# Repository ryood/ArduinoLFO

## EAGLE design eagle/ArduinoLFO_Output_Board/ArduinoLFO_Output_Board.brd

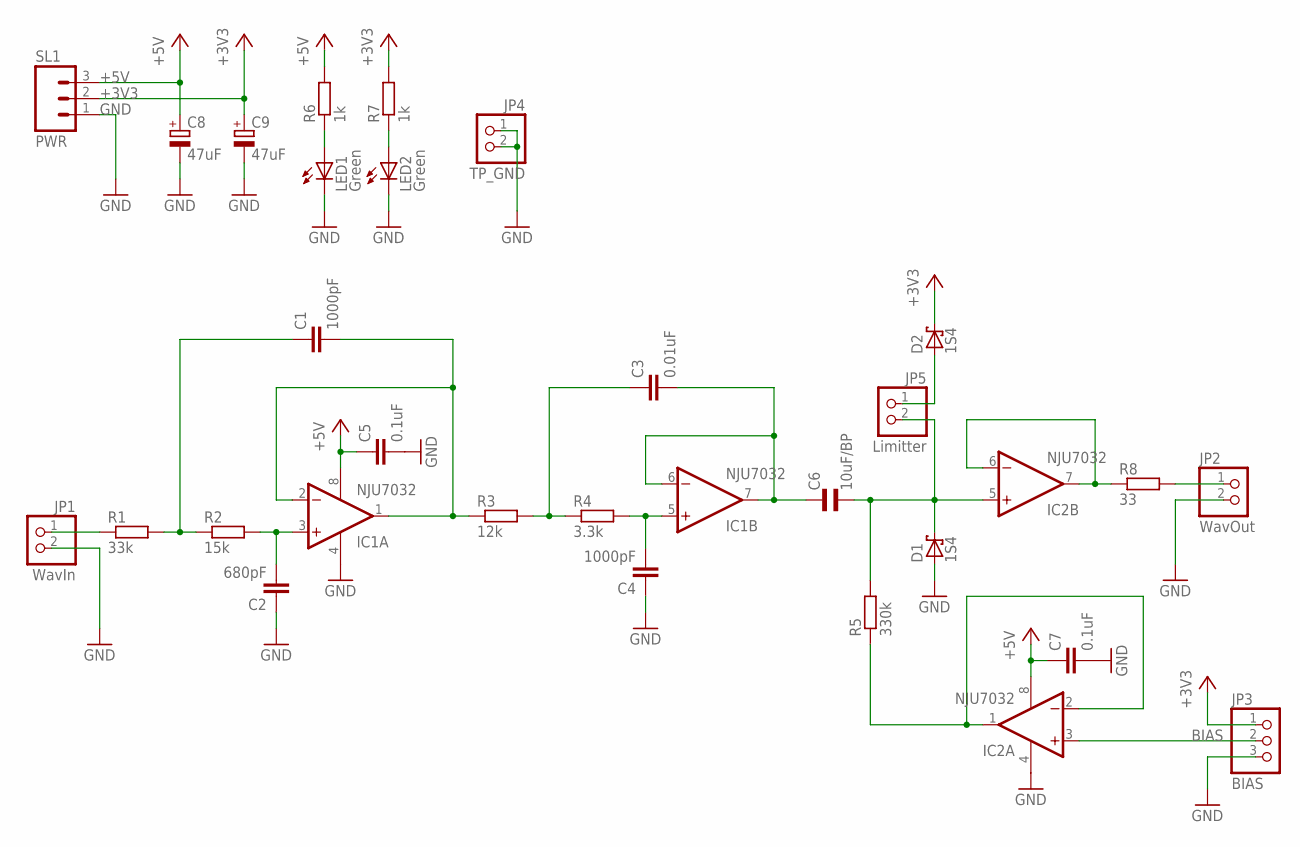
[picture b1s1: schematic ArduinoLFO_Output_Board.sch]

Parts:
C1, C4: 1000pF; C050-025X075
C2: 680pF; C050-030X075
C3: 0.01uF; C050-025X075
C5, C7: 0.1uF; C025-024X044
C6: 10uF/BP; E5-8,5
C8, C9: 47uF; E2,5-6
D1, D2: 1S4; DO35-7
IC1, IC2: NJU7032; DIL08
JP1: WavIn; 1X02
JP2: WavOut; 1X02
JP3: BIAS; 1X03
JP4: TP_GND; 1X02
JP5: Limitter; 1X02
LED1, LED2: Green; LED3MM
R1: 33k; 0207/7
R2: 15k; 0207/7
R3: 12k; 0207/7
R4: 3.3k; 0207/7
R5: 330k; 0207/7
R6, R7: 1k; 0207/7
R8: 33; 0207/7
SL1: PWR; 03PA

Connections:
+3V3: C9.+, D2.C, JP3.1, R7.2, SL1.2
+5V: C5.1, C7.1, C8.+, IC1.8 (V+), IC2.8 (V+), R6.2, SL1.3
BIAS: IC2.3 (+IN), JP3.2
GND: C2.1, C4.1, C5.2, C7.2, C8.-, C9.-, D1.A, IC1.4 (V-), IC2.4 (V-), JP1.2, JP2.2, JP3.3, JP4.1, JP4.2, LED1.K (C), LED2.K (C), SL1.1
unnamed: JP1.1, R1.1
unnamed: C1.1, R1.2, R2.1
unnamed: C2.2, IC1.3 (+IN), R2.2
unnamed: C1.2, IC1.1 (OUT), IC1.2 (-IN), R3.1
unnamed: C3.1, R3.2, R4.1
unnamed: C4.2, IC1.5 (+IN), R4.2
unnamed: C3.2, C6.1, IC1.6 (-IN), IC1.7 (OUT)
unnamed: C6.2, D1.C, IC2.5 (+IN), JP5.2, R5.2
unnamed: IC2.6 (-IN), IC2.7 (OUT), R8.1
unnamed: IC2.1 (OUT), IC2.2 (-IN), R5.1
unnamed: JP2.1, R8.2
unnamed: LED1.A, R6.1
unnamed: LED2.A, R7.1
unnamed: D2.A, JP5.1

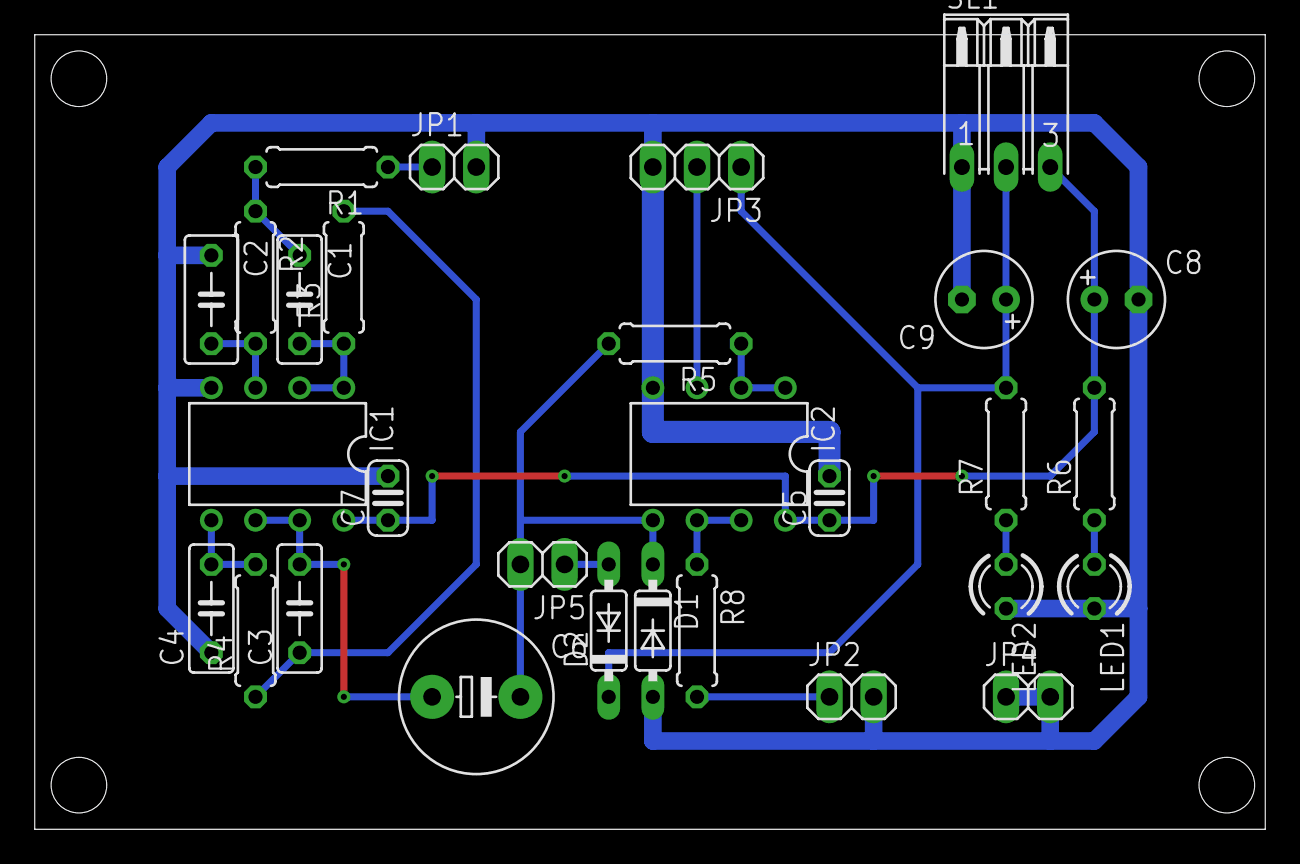
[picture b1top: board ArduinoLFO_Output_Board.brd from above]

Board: 2 copper layers, 70.8 x 45.7 mm, 29 parts (0 on the bottom side), 18 nets.

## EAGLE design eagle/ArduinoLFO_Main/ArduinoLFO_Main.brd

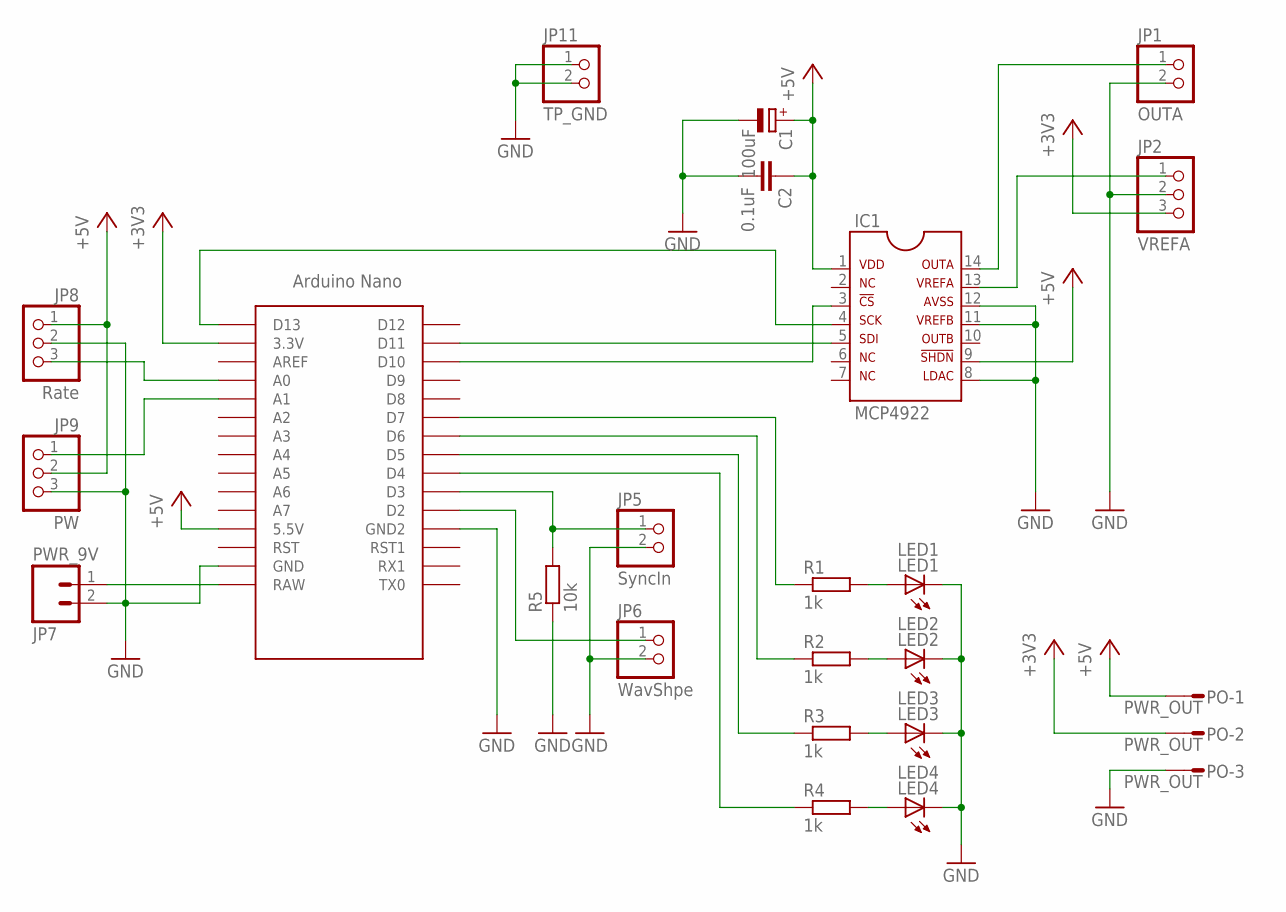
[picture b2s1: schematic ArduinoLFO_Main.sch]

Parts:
C1: 100uF; E2,5-7
C2: 0.1uF; C025-024X044
IC1: MCP4922
JP1: OUTA; 1X02
JP2: VREFA; 1X03
JP5: SyncIn; 1X02
JP6: WavShpe; 1X02
JP7: PWR_9V; 02PA
JP8: Rate; 1X03
JP9: PW; 1X03
JP11: TP_GND; 1X02
LED1: LED1; LED3MM
LED2: LED2; LED3MM
LED3: LED3; LED3MM
LED4: LED4; LED3MM
PO: PWR_OUT; 03PA
R1, R2, R3, R4: 1k; 0204V
R5: 10k; 0207/7
U$1: NANO

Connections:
+3V3: JP2.3, PO.2, U$1.3.3V
+5V: C1.+, C2.1, IC1.1, IC1.9, JP8.1, JP9.2, PO.1, U$1.5V (5.5V)
GND: C1.-, C2.2, IC1.8, IC1.11, IC1.12, JP1.2, JP2.2, JP5.2, JP6.2, JP7.2, JP8.2, JP9.3, JP11.1, JP11.2, LED1.K (C), LED2.K (C), LED3.K (C), LED4.K (C), PO.3, R5.1, U$1.GND, U$1.GND1 (GND2)
unnamed: IC1.4, U$1.D13
unnamed: IC1.5, U$1.D11
unnamed: IC1.3, U$1.D10
unnamed: JP8.3, U$1.A0
unnamed: IC1.14, JP1.1
unnamed: IC1.13, JP2.1
unnamed: JP9.1, U$1.A1
unnamed: JP7.1, U$1.RAW
unnamed: LED1.A, R1.2
unnamed: LED2.A, R2.2
unnamed: LED3.A, R3.2
unnamed: LED4.A, R4.2
unnamed: R1.1, U$1.D7
unnamed: R2.1, U$1.D6
unnamed: R3.1, U$1.D5
unnamed: R4.1, U$1.D4
unnamed: JP5.1, R5.2, U$1.D3
unnamed: JP6.1, U$1.D2

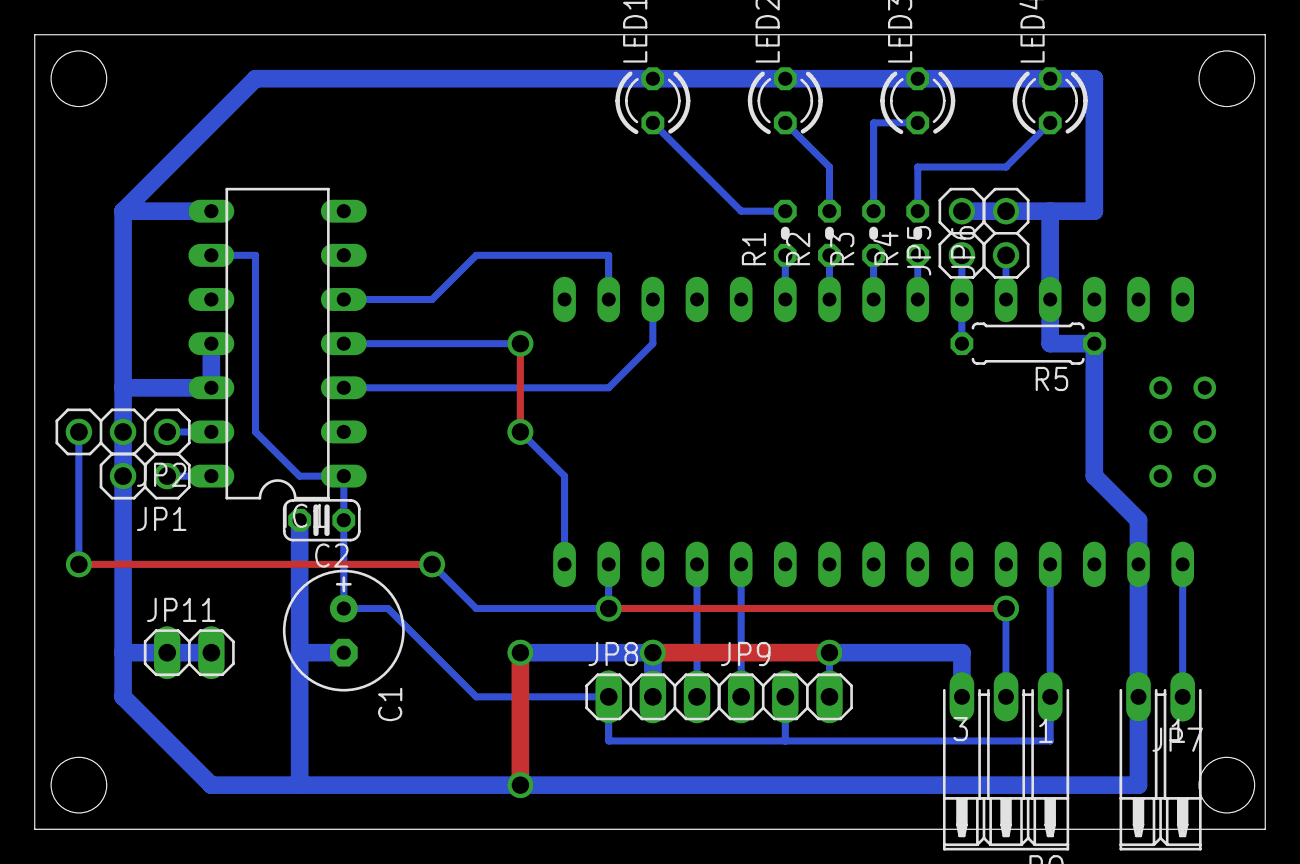
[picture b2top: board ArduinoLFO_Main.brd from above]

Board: 2 copper layers, 70.8 x 45.7 mm, 22 parts (0 on the bottom side), 21 nets.

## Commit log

2018-01-19 Clean up MCP4922_LFO.ino
2018-01-21 clean up
2018-01-21 Add Arduino LFO ブロック図
2018-01-21 12bit WaveTable
2018-01-23 Add GenWaveTable (Visual Studio 2013)
2018-01-23 Impl. DDS Sin, Tri, Sqr, SawUp, SawDown (12bit, 2048 values)
2018-01-26 Testing the wave shape button
2018-01-26 ButtonWaveShape as Interrupt
2018-01-26 use LED pin as PORT
2018-01-26 Show the wave shape on LEDs
2018-01-26 AnalogRead the value of pulse width. (dummy)
2018-01-28 MCP4922_DDS_WaveTableSize_Test
2018-01-31 Add LPF
2018-02-04 Add Output Board
2018-02-08 Impl. SQR pulse width
2018-02-08 4LEDs
2018-02-08 SyncIn
2018-02-08 Add: random_function_TimeTest
2018-02-08 use phaccu (not wave table) for saw wave
2018-02-08 use 12bit 4k table
2018-02-08 Add eagle files
2018-02-14 Board Design
2018-02-25 Main Boardはんだ付け完了
2018-02-25 ~50Hz, PulseWidth scope
2018-03-16 ArduinoLFO OutputBoard テスト表
2018-03-19 はんだ付け完了
2018-03-22 Add: ケース内配線図
2018-03-27 Update: ArduinoLFOケース内配線
2018-04-01 Update: the cad data of the Case .
2018-04-02 Rebuild 'GenWaveTable' with Visual Studio 2017
2018-04-08 Add: MCP4922_OSC
2018-05-05 10s Cycle ~ 10Hz
2018-05-05 Sampling Rate: 25kHz
2018-05-06 Sampling Rate & MAX_RATE
